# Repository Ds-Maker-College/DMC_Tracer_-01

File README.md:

# DMC Tracer 01 Nano

This is an open-source robot for the DMC Remote Robot contest.

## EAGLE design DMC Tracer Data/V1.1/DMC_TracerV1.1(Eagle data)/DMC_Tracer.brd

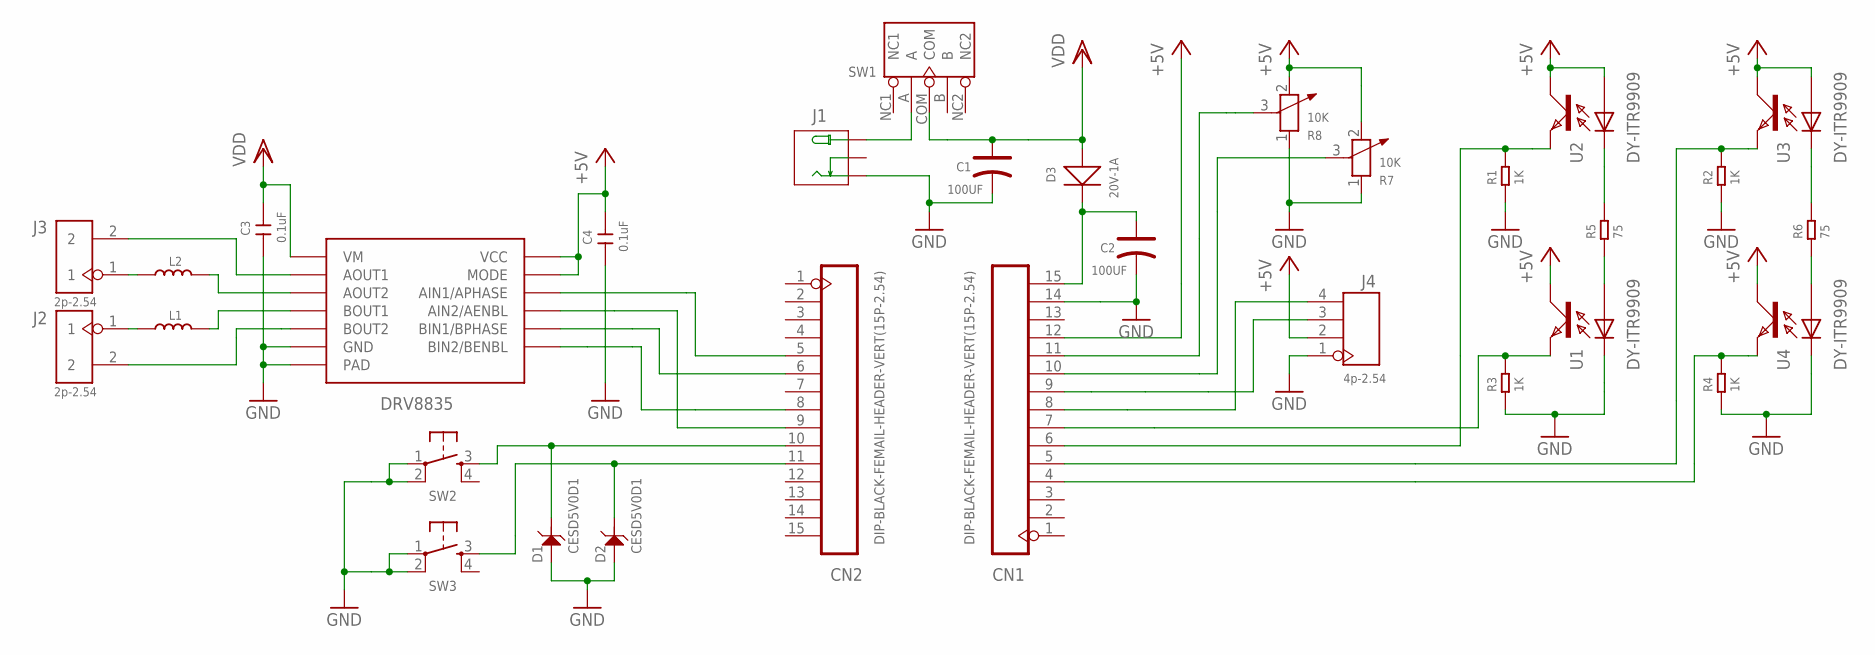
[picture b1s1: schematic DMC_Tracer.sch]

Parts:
C1, C2: 100UF; ELECTRO-SMD-C-6MM
C3, C4: 0.1uF; C0603
CN1, CN2: DIP-BLACK-FEMAIL-HEADER-VERT(15P-2.54); H15-2.54
D1, D2: CESD5V0D1; SOD-123
D3: 20V-1A; SOD-123
J1: DC-005; 3P-L14.2*W11.0*H9.0MM
J2, J3: 2p-2.54; H2-2.54
J4: 4p-2.54; H4-2.54
L1, L2: SMD-INDUCTOR(2P-8X8MM); L8040
R1, R2, R3, R4: 1K; R0805
R5, R6: 75; R0805
R7, R8: 10K; ADJR3-7.0X7.0X5.0MM
SW1: DIP-TOGGLE-SWITCH-ON-ON(3+2P-8.8X4.6MM)-90D; SW5-2.0-8.8X4.4X4.7MM-90D
SW2, SW3: T-SWITCH-10-SEEED; B3F-10XX-SEEED
U1, U2, U3, U4: DY-ITR9909
U$1: DRV8835; WSON12

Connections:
+5V: C4.1, CN1.12, J4.2, R7.2, R8.2, U1.C, U2.A, U2.C, U3.A, U3.C, U4.C, U$1.P$11 (MODE), U$1.P$12 (VCC)
AOUT1: L2.2, U$1.P$3 (AOUT2)
AOUT2: J3.2, U$1.P$2 (AOUT1)
BOUT1: J2.2, U$1.P$5 (BOUT2)
BOUT2: L1.2, U$1.P$4 (BOUT1)
GND: C1.-, C2.-, C3.2, C4.2, CN1.14, D1.+ (1), D2.+ (1), J1.-1 (-), J4.1, R1.1, R2.1, R3.1, R4.1, R7.1, R8.1, SW2.1, SW2.2 (P1), SW3.1, SW3.2 (P1), U1.K, U4.K, U$1.P$6 (GND), U$1.P$13 (PAD), U$1.P$14 (GND)
unnamed: CN1.8, J4.4
unnamed: CN1.9, J4.3
unnamed: CN2.10, D1.- (2), SW2.3 (S)
unnamed: CN2.11, D2.- (2), SW3.3 (S)
unnamed: CN1.10, R7.3
unnamed: CN1.6, R1.2, U2.E
unnamed: CN1.5, R2.2, U3.E
unnamed: CN1.4, R4.2, U4.E
unnamed: R5.2, U2.K
unnamed: J1.+, SW1.A
unnamed: CN2.5, U$1.P$10 (AIN1/APHASE)
unnamed: R6.2, U3.K
unnamed: J3.1, L2.1
unnamed: R6.1, U4.A
unnamed: R5.1, U1.A
unnamed: CN2.6, U$1.P$8 (BIN1/BPHASE)
unnamed: CN2.9, U$1.P$9 (AIN2/AENBL)
unnamed: CN2.8, U$1.P$7 (BIN2/BENBL)
unnamed: J2.1, L1.1
unnamed: C2.+, CN1.15, D3.-
unnamed: CN1.11, R8.3
unnamed: CN1.7, R3.2, U1.E
VDD: C1.+, C3.1, D3.+, SW1.COM, U$1.P$1 (VM)

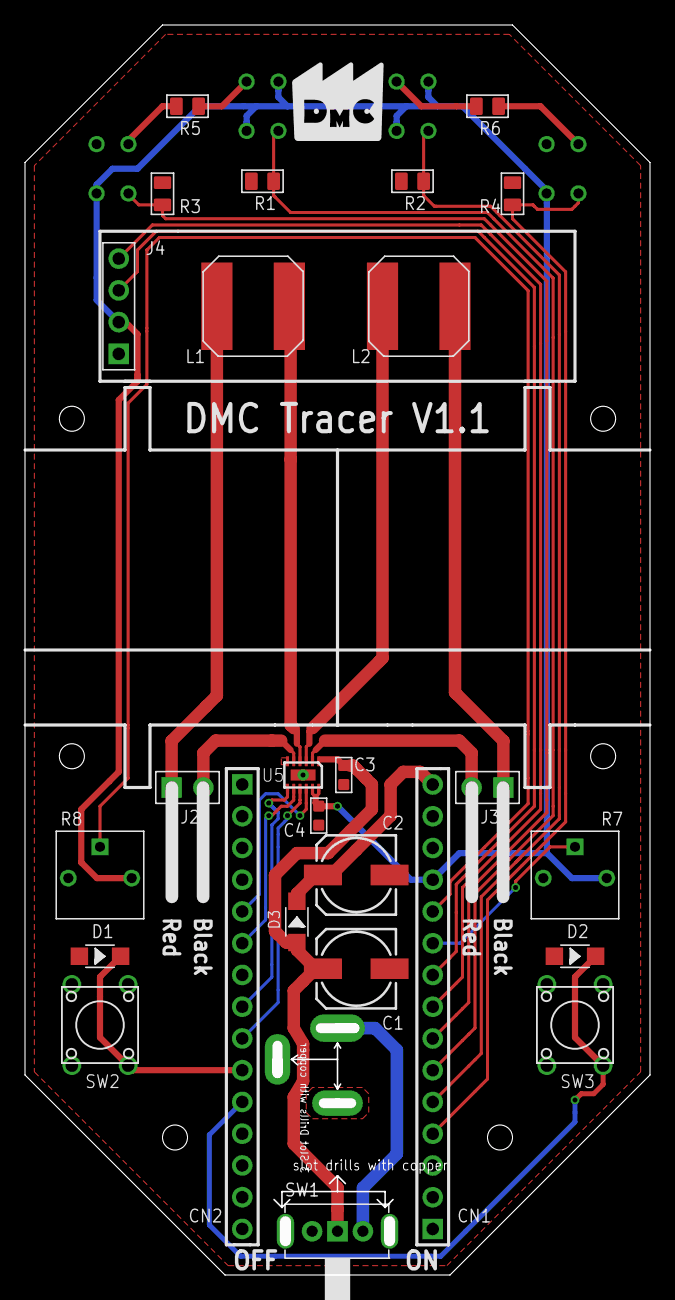
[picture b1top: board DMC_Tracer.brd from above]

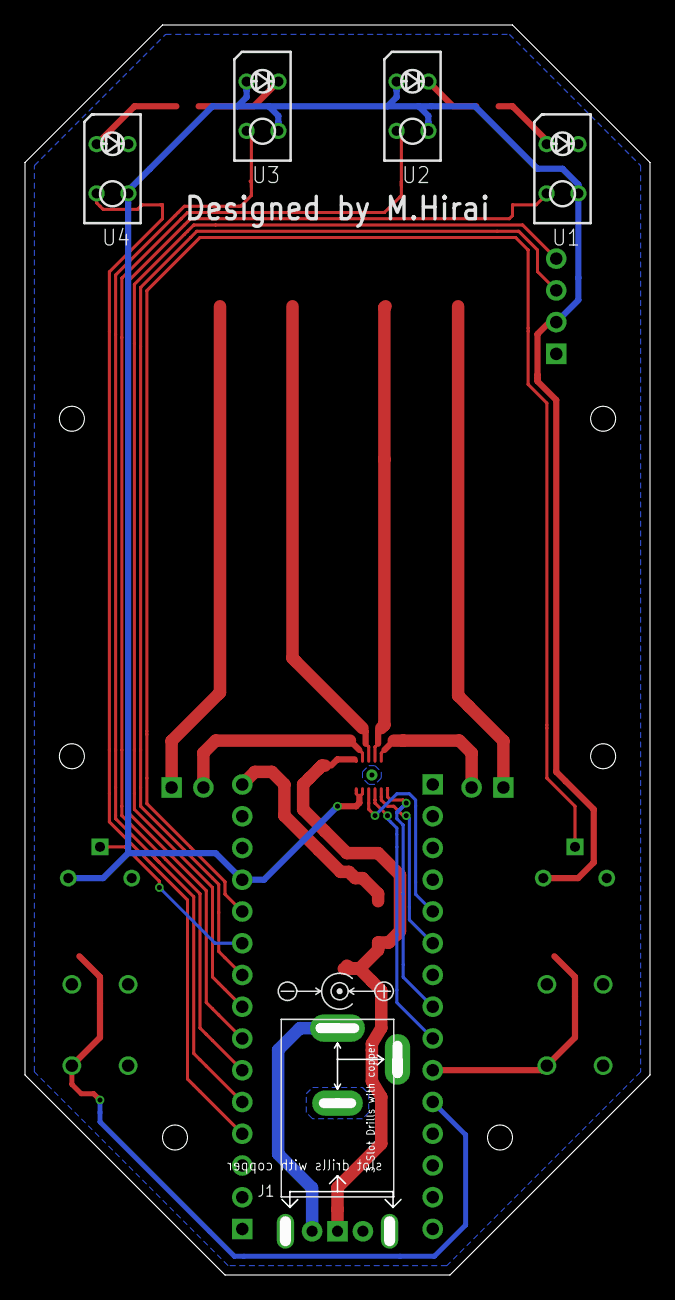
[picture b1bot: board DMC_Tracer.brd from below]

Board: 2 copper layers, 50.0 x 100.0 mm, 31 parts (5 on the bottom side), 29 nets.

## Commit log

2022-12-29 Create LICENSE
